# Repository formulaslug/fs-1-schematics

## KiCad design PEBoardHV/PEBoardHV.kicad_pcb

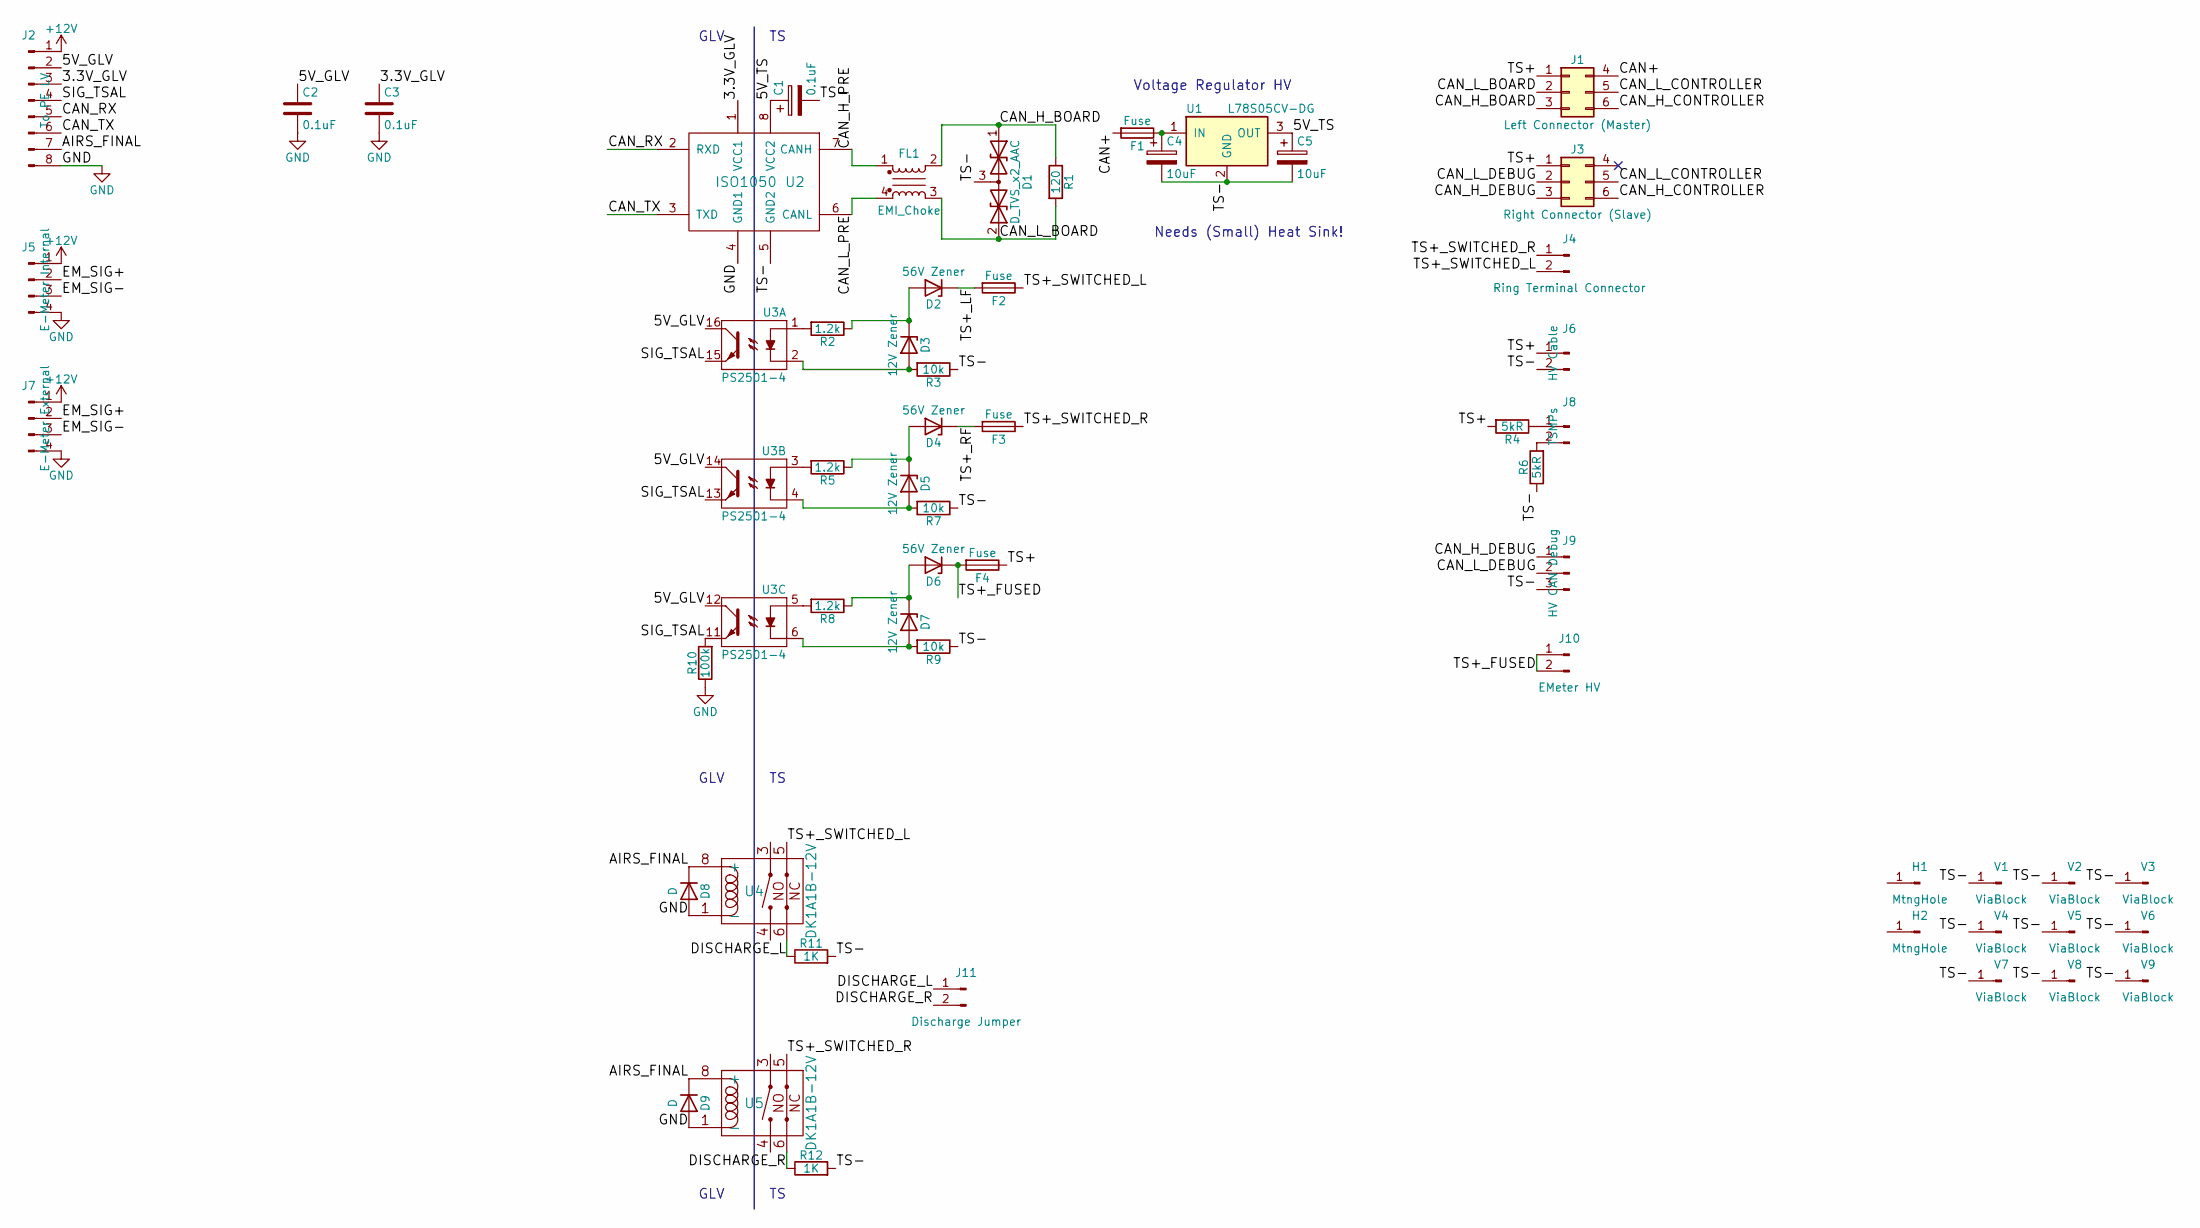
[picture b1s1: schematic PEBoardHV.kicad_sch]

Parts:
C1, C3: 0.1uF; C_Disc_D4.3mm_W1.9mm_P5.00mm
C2: 0.1uF; C_Disc_D3.0mm_W1.6mm_P2.50mm
C4, C5: 10uF; CP_Radial_D5.0mm_P2.50mm
D1: D_TVS_x2_AAC; SOT-23_Handsoldering
D2, D4, D6: 56V Zener; D_A-405_P7.62mm_Horizontal
D3, D5, D7: 12V Zener; D_A-405_P7.62mm_Horizontal
D8, D9: D; D_1206
F1, F2, F3, F4: Fuse; SMD Fuse
FL1: EMI_Choke; L_CommonMode_Choke
H1, H2: MtngHole; MountingHole_4.5mm
J1: Left Connector (Master); Molex_NanoFit_2x03x2.50mm_Straight
J2: To PE LV; Molex_NanoFit_2x04x2.50mm_Straight
J3: Right Connector (Slave); Molex_NanoFit_2x03x2.50mm_Straight
J4: Ring Terminal Connector; Molex_NanoFit_1x02x2.50mm_Straight
J5: E-Meter Internal; Molex_NanoFit_2x02x2.50mm_Straight
J6: HV Cable; Molex_NanoFit_1x02x2.50mm_Straight
J7: E-Meter External; DT15-4P
J8: TSMPs; DT15-2P
J9: HV CAN Debug; Molex_NanoFit_1x03x2.50mm_Straight
J10: EMeter HV; Molex_NanoFit_1x02x2.50mm_Straight
J11: Discharge Jumper; Pin_Header_Straight_2x01_Pitch2.54mm
R1: 120; R_0805_HandSoldering
R2, R5, R8: 1.2k; R_Axial_DIN0207_L6.3mm_D2.5mm_P10.16mm_Horizontal
R3, R7, R9: 10k; R_Axial_DIN0411_L9.9mm_D3.6mm_P12.70mm_Horizontal
R4, R6: 5kR; R_Axial_DIN0414_L11.9mm_D4.5mm_P20.32mm_Horizontal
R10: 100k; R_Axial_DIN0207_L6.3mm_D2.5mm_P10.16mm_Horizontal
R11, R12: 1K; TO-220-2_Horizontal_HeatSunk
U1: L78S05CV-DG; TO-220-3_Horizontal_HeatSunk
U2: ISO1050; DIP-8_W8.89mm_SMDSocket_LongPads
U3: PS2501-4; DIP-16_W7.62mm
U4, U5: DK1A1B-12V
V1, V2, V3, V4, V5, V6, V7, V8, V9: ViaBlock; ViaBlock-0.8mm

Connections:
+12V: J2.1, J5.1, J7.1
/3.3V_GLV: C3.1, J2.3, U2.1 (VCC1)
/5V_GLV: C2.1, J2.2, U3.12, U3.14, U3.16
/5V_TS: C1.1, C5.1, U1.3 (OUT), U2.8 (VCC2)
/AIRS_FINAL: D8.1 (K), D9.1 (K), J2.7, U4.8 (+), U5.8 (+)
/CAN+: F1.2, J1.4
/CAN_H_BOARD: D1.1 (A1), FL1.2, J1.3, R1.1
/CAN_H_CONTROLLER: J1.6, J3.6
/CAN_H_DEBUG: J3.3, J9.1
/CAN_H_PRE: FL1.1, U2.7 (CANH)
/CAN_L_BOARD: D1.2 (A2), FL1.3, J1.2, R1.2
/CAN_L_CONTROLLER: J1.5, J3.5
/CAN_L_DEBUG: J3.2, J9.2
/CAN_L_PRE: FL1.4, U2.6 (CANL)
/CAN_RX: J2.5, U2.2 (RXD)
/CAN_TX: J2.6, U2.3 (TXD)
/DISCHARGE_L: J11.1, R11.1, U4.6
/DISCHARGE_R: J11.2, R12.1, U5.6
/EM_SIG+: J5.2, J7.2
/EM_SIG-: J5.3, J7.3
/SIG_TSAL: J2.4, R10.2, U3.11, U3.13, U3.15
/TS+: F4.1, J1.1, J3.1, J6.1, R4.2
/TS+_FUSED: D6.1 (K), F4.2, J10.1, J10.2
/TS+_LF: D2.1 (K), F2.2
/TS+_RF: D4.1 (K), F3.2
/TS+_SWITCHED_L: F2.1, J4.2, U4.5
/TS+_SWITCHED_R: F3.1, J4.1, U5.5
/TS-: C1.2, C4.2, C5.2, D1.3 (common), J6.2, J9.3, R3.1, R6.1, R7.1, R9.1, R11.2, R12.2, U1.2 (GND), U2.5 (GND2), V1.1, V2.1, V3.1, V4.1, V5.1, V6.1, V7.1, V8.1, V9.1
GND: C2.2, C3.2, D8.2 (A), D9.2 (A), J2.8, J5.4, J7.4, R10.1, U2.4 (GND1), U4.1 (-), U5.1 (-)
unnamed: C4.1, F1.1, U1.1 (IN)
unnamed: D2.2 (A), D3.1 (K), R2.1
unnamed: D3.2 (A), R3.2, U3.2
unnamed: D4.2 (A), D5.1 (K), R5.1
unnamed: D5.2 (A), R7.2, U3.4
unnamed: D6.2 (A), D7.1 (K), R8.1
unnamed: D7.2 (A), R9.2, U3.6
unnamed: J8.1, R4.1
unnamed: J8.2, R6.2
unnamed: R2.2, U3.1
unnamed: R5.2, U3.3
unnamed: R8.2, U3.5

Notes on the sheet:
Voltage Regulator HV
GLV TS
Needs (Small) Heat Sink!

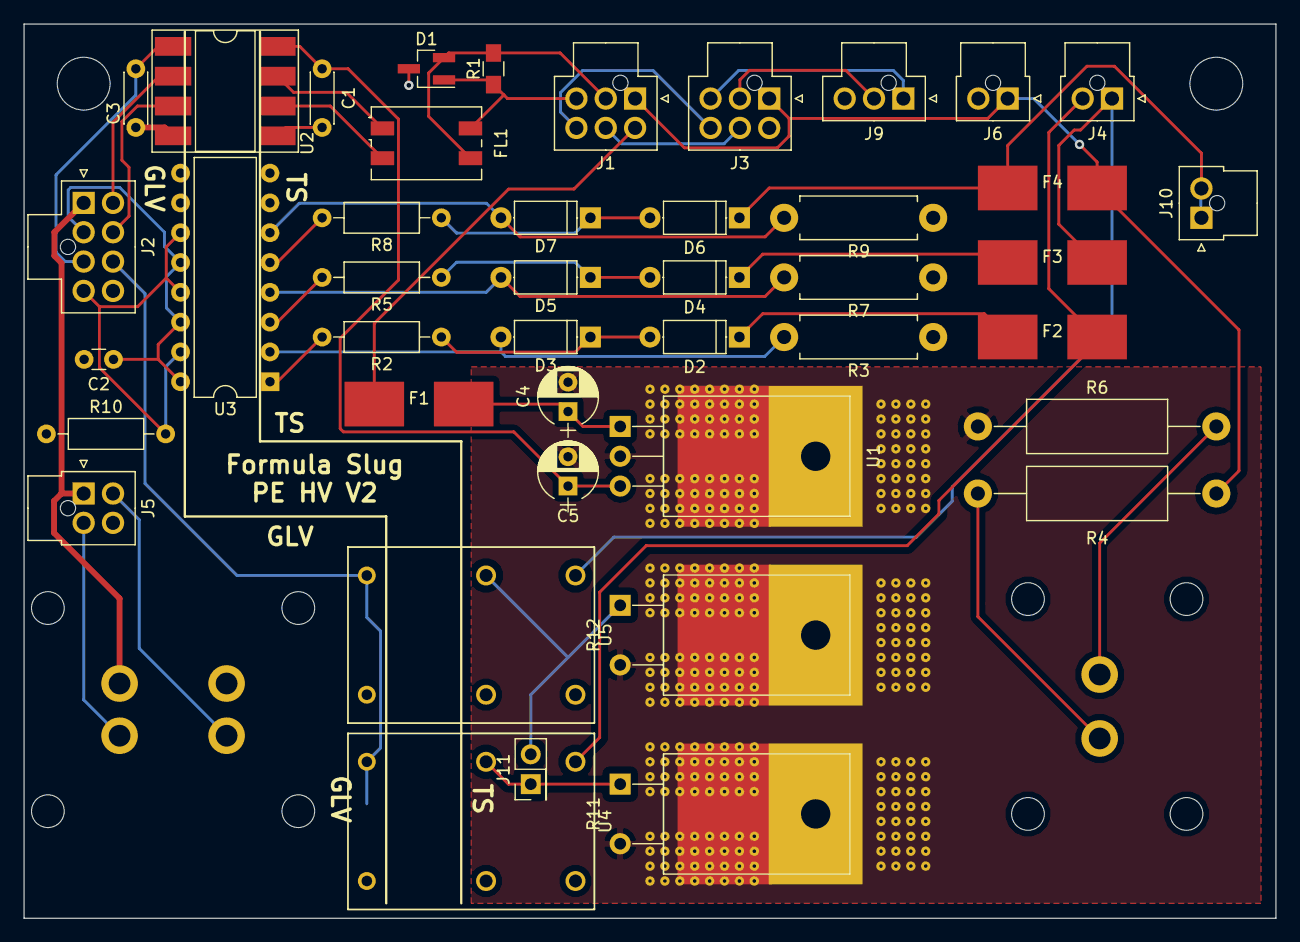
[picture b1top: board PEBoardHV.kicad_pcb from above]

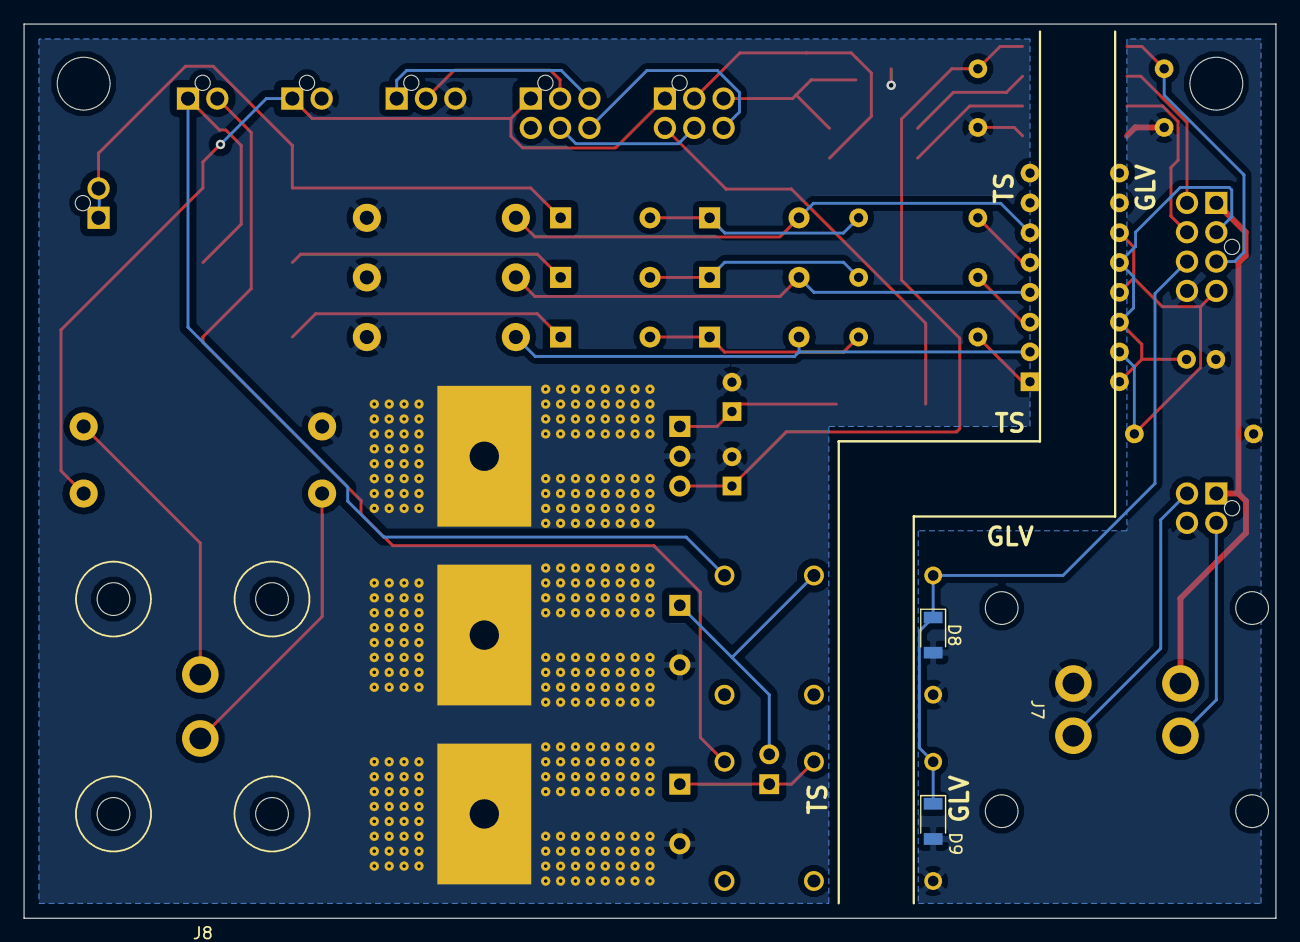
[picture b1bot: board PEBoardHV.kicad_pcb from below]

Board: 2 copper layers, 106.7 x 76.2 mm, 58 parts (4 on the bottom side), 41 nets.

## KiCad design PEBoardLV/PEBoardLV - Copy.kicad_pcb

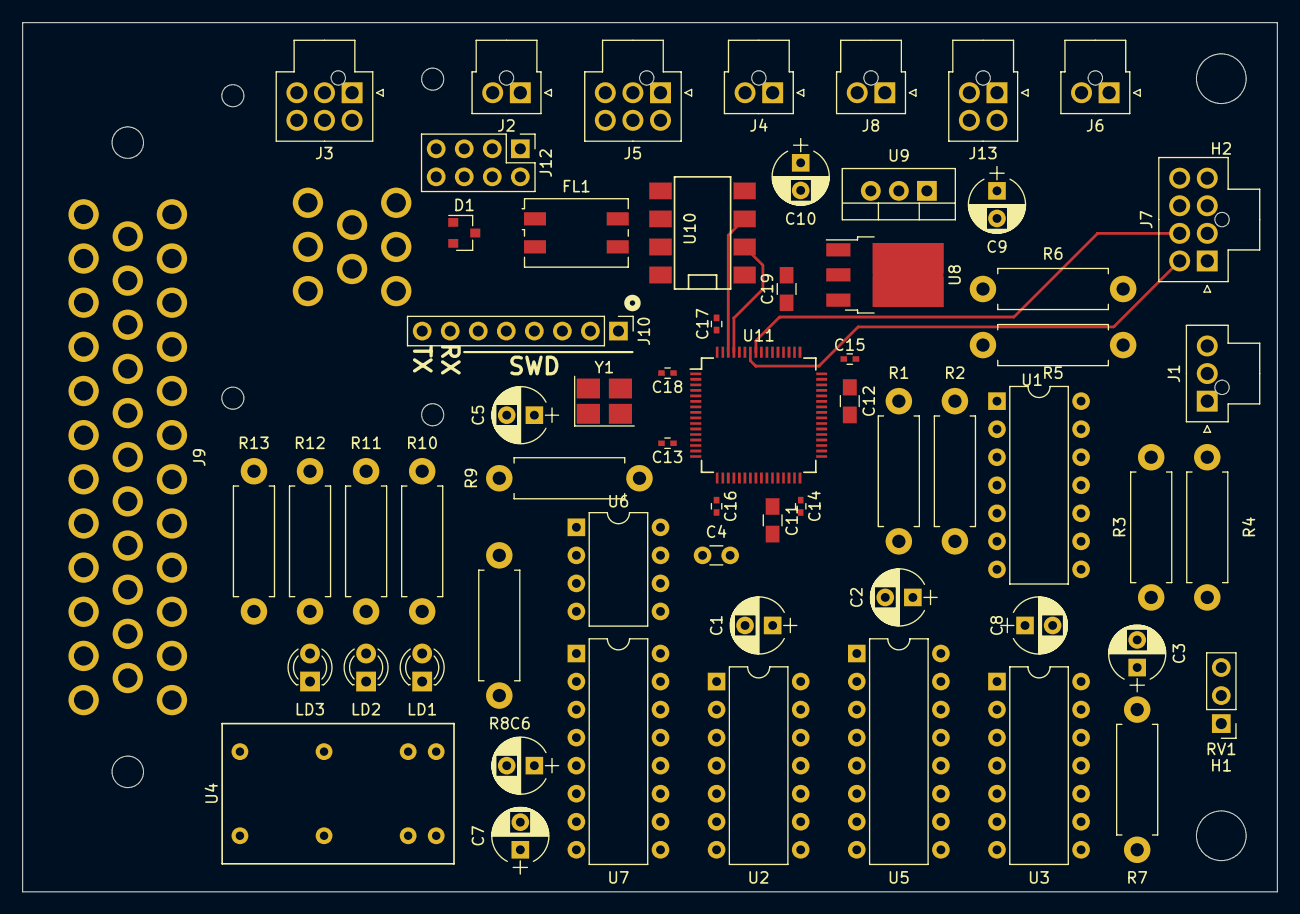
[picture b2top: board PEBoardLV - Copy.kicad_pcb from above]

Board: 2 copper layers, 113.7 x 78.7 mm, 65 parts (1 on the bottom side), 92 nets.

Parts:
C1, C2, C6, C7, C8: CP; CP_Radial_D5.0mm_P2.50mm
C3, C5, C9, C10: 10uF; CP_Radial_D5.0mm_P2.50mm
C4: 0.1uF; C_Disc_D3.0mm_W1.6mm_P2.50mm
C11, C12: 2.2uF; C_0805_HandSoldering
C13, C14, C15, C16, C17, C18: 0.1uF; C_0402
C19: 4.7uF; C_0805_HandSoldering
D1: D_TVS_x2_AAC; SOT-23
FL1: EMI_Filter_CommonMode; L_CommonMode_Wuerth_WE-SL2
H1, H2: MtngHole; MountingHole_4.5mm
J1: BSPD Test Jumper; Molex_NanoFit_1x03x2.50mm_Straight
J2: Beam Interlock; Molex_NanoFit_1x02x2.50mm_Straight
J3: To HV Interlocks; Molex_NanoFit_2x03x2.50mm_Straight
J4: To Left Panel; Molex_NanoFit_1x02x2.50mm_Straight
J5: To Right Panel; Molex_NanoFit_2x03x2.50mm_Straight
J6: To Brake Light; Molex_NanoFit_1x02x2.50mm_Straight
J7: To PE HV; Molex_NanoFit_2x04x2.50mm_Straight
J8: BSPD Reset; Molex_NanoFit_1x02x2.50mm_Straight
J9: Main LV Connector; Ampseal - 35 pin
J10: SWD Header; Pin_Header_Straight_1x08_Pitch2.54mm
J11: ECU Debug Connector; Ampseal-776276-1
J12: Extra Pin Header; Pin_Header_Straight_2x04_Pitch2.54mm
J13: To TSAL; Molex_NanoFit_2x02x2.50mm_Straight
LD1, LD2, LD3: LED; LED_D3.0mm
R1, R2, R3, R4, R5, R6: R; R_Axial_DIN0411_L9.9mm_D3.6mm_P12.70mm_Horizontal
R7: 100k; R_Axial_DIN0411_L9.9mm_D3.6mm_P12.70mm_Horizontal
R8: 4.7kR; R_Axial_DIN0411_L9.9mm_D3.6mm_P12.70mm_Horizontal
R9: 18k; R_Axial_DIN0411_L9.9mm_D3.6mm_P12.70mm_Horizontal
R10, R11, R12: 330; R_Axial_DIN0411_L9.9mm_D3.6mm_P12.70mm_Horizontal
R13: 2.2k; R_Axial_DIN0411_L9.9mm_D3.6mm_P12.70mm_Horizontal
RV1: POT; Pin_Header_Straight_1x03_Pitch2.54mm
U1: MCP6004; DIP-14_W7.62mm
U2: 4072; DIP-14_W7.62mm
U3: 4071; DIP-14_W7.62mm
U4: DE1A1B-L2-12V
U5: 74HC595; DIP-16_W7.62mm
U6: LM555N; DIP-8_W7.62mm
U7: SN754410; DIP-16_W7.62mm
U8: NCP1117DT33RKG; TO-252-3_TabPin2
U9: L78S05CV-DG; TO-220-3_Vertical
U10: ISO1050; DIP-8_SMD
U11: STM32F405; LQFP-64_10x10mm_Pitch0.5mm
Y1: 8MHz; Crystal_SMD_3225-4pin_3.2x2.5mm_HandSoldering

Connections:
+3V3: C13.1, C14.1, C15.1, C16.1, C17.1, C18.1, C19.1, J7.3, J9.14, J9.20, J10.1, J11.1, R5.1, R13.1, RV1.1, U1.9, U8.3, U10.1, U11.1, U11.13, U11.19, U11.32, U11.48, U11.64, Y1.4
+5V: C1.1, C2.1, C6.1, C8.1, C10.1, J7.2, R7.1, R8.1, U1.4, U2.14, U3.14, U5.10, U5.16, U6.4, U6.8, U7.1, U7.9, U7.16, U9.3, U10.8
+12V: C7.1, C9.1, J7.1, J9.1, J9.2, J9.23, J13.1, U7.8, U8.1, U9.1
/5V_BMS: J9.9, R2.2, R3.1
/12V_LVMS: J5.2, J9.24
/12V_SRC: J5.1, J9.3
/AIRS_3PHASE_OUT: J3.4, J3.5
/AIRS_ACC_OUT: J4.1, J9.7
/AIRS_BEAM_OUT: J2.2, J3.1
/AIRS_BOTS_OUT: J9.13, U4.5
/AIRS_BSPD_OUT: J2.1, U4.6
/AIRS_DASH_OUT: J9.12, J9.30
/AIRS_FINAL: J5.4, J7.7, J9.8
/AIRS_LEFTESTOP_OUT: J4.2, J5.3
/AIRS_PEINTERLOCKS_OUT: J3.6, J9.6
/BRAKELT_H: J6.1, U7.11, U7.14
/BSPD_BRAKE: U1.7, U3.2
/BSPD_CURRENT: U1.1, U3.1
/BSPD_FLT: U3.4, U7.2
/BSPD_FLT_H: U4.8, U7.3
/BSPD_FLT_LATCHED: U4.3, U11.35
/BSPD_RESET: J8.1, U4.7
/BSPD_SIG: U3.3, U5.14
/BUTTON_1: J9.27, U11.30
/BUTTON_2: J9.28, U11.33
/BUTTON_3: J9.29, U11.34
/CAN_H: D1.2, FL1.2, J9.4, J9.25
/CAN_L: D1.1, FL1.4, J9.5, J9.26
/CAN_RX_GLV: U10.2, U11.61
/CAN_RX_TS: J7.6, U11.57
/CAN_TX_GLV: U10.3, U11.62
/CAN_TX_TS: J7.5, U11.58
/CLK: U5.11, U5.12, U6.3
/LED_AMS: J9.31, U11.41
/LED_BSPD: J9.33, U11.37
/LED_IMD: J9.32, U11.50
/NRST: J10.5, J11.5, U11.7
/PA4: J12.5, U11.20
/PA5: J12.6, U11.21
/PA7: J12.7, U11.23
/PC0: J12.1, U11.8
/PC1: J12.2, U11.9
/PC2: J12.3, U11.10
/PC3: J12.4, U11.11
/PC4: J12.8, U11.24
/SIG_APPS_A: J9.15, U11.16
/SIG_APPS_B: J9.18, U11.17
/SIG_BRAKELT: U7.10, U7.15, U11.40
/SIG_BSE: J9.21, U1.6, U11.15
/SIG_CURRENT: J1.3, J9.10
/SIG_RTDS: J13.3, U11.39
/SIG_STEER: J9.34, U11.22
/SIG_TSAL: J7.4, J13.2
/STATUS_LED_1: R10.2, U11.28
/STATUS_LED_2: R11.2, U11.27
/STATUS_LED_3: R12.2, U11.26
/SWCLK: J10.2, J11.2, U11.49
/SWDIO: J10.4, J11.4, U11.46
/SWO: J10.6, J11.6, U11.55
/TIMER: U1.8, U7.7
/TIMER_H: U4.1, U4.2, U7.6
/UART_RX: J10.7, J11.7, U11.52
/UART_TX: J10.8, J11.8, U11.51
/VCAP_1: C11.1, U11.31
/VCAP_2: C12.1, U11.47
/XTAL: U11.5, Y1.3
GND: C1.2, C2.2, C3.2, C4.2, C5.2, C6.2, C7.2, C8.2, C9.2, C10.2, C11.2, C12.2, C13.2, C14.2, C15.2, C16.2, C17.2, C18.2, C19.2, D1.3, J5.5, J6.2, J7.8, J8.2, J9.11, J9.16, J9.19, J9.22, J9.35, J10.3, J11.3, J13.4, LD1.1, LD2.1, LD3.1, R1.1, R4.2, R6.2, RV1.3, U1.11, U2.7, U3.7, U4.4, U5.8, U5.13, U6.1, U7.4, U7.5, U7.12, U7.13, U8.2, U9.2, U10.4, U10.5, U11.12, U11.18, U11.29, U11.60, U11.63, Y1.2
unnamed: C3.1, R7.2, U1.10
unnamed: C4.1, U6.5
unnamed: C5.1, R9.2, U6.2, U6.6
unnamed: FL1.1, U10.7
unnamed: FL1.3, U10.6
unnamed: J1.1, R3.2, R4.1
unnamed: J1.2, U1.2
unnamed: J3.2, J3.3
unnamed: J9.17, R13.2
unnamed: LD1.2, R10.1
unnamed: LD2.2, R11.1
unnamed: LD3.2, R12.1
unnamed: R1.2, R2.1, U1.3
unnamed: R5.2, R6.1, RV1.2, U1.5
unnamed: R8.2, R9.1, U6.7
unnamed: U2.1, U3.5
unnamed: U2.2, U5.15
unnamed: U2.3, U5.1
unnamed: U2.4, U5.2
unnamed: U2.5, U5.3
unnamed: U2.9, U5.4
unnamed: U2.10, U5.5
unnamed: U2.11, U5.6
unnamed: U2.12, U5.7
unnamed: U2.13, U3.6

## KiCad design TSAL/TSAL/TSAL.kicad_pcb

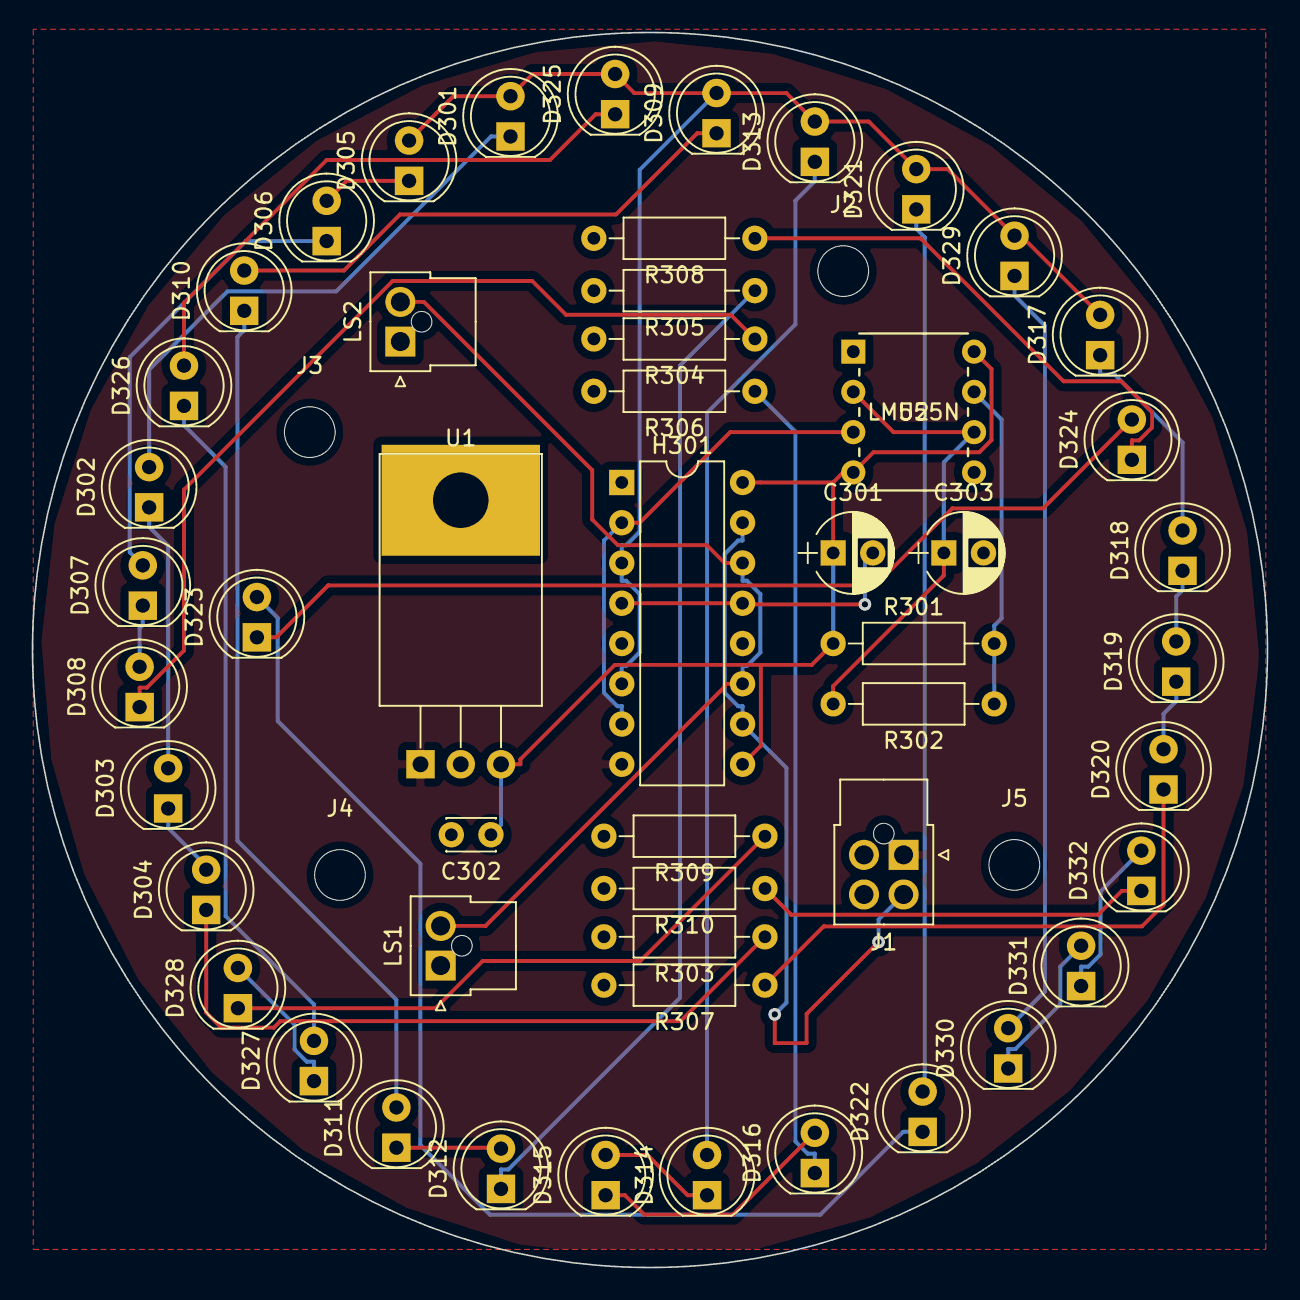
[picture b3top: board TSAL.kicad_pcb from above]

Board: 2 copper layers, 77.9 x 77.9 mm, 55 parts (0 on the bottom side), 41 nets.

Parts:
C301, C303: 10uF; CP_Radial_D5.0mm_P2.50mm
C302: .47uF; C_Disc_D3.0mm_W2.0mm_P2.50mm
D301, D302, D303, D304, D305, D306, D307, D308, D309, D310, D311, D312, D313, D314, D315, D316, D317, D318, D319, D320, D321, D322, D323, D324, D325, D326, D327, D328, D329, D330, D331, D332: Led_Small; LED_D5.0mm
H301: SN754410; DIP-16_W7.62mm
J1: CONN_01X04; Molex_NanoFit_2x02x2.50mm_Straight
J2, J3, J4, J5: Conn_01x01; MountingHole_3.2mm_M3
LS1, LS2: RTDS Piezo; Molex_NanoFit_1x02x2.50mm_Straight
R301, R302: 15K; R_Axial_DIN0207_L6.3mm_D2.5mm_P10.16mm_Horizontal
R303, R304, R305, R306, R307, R308, R309, R310: 180; R_Axial_DIN0207_L6.3mm_D2.5mm_P10.16mm_Horizontal
U1: L78S05CV-DG; TO-220-3_Horizontal_HeatSunk
U2: LM555N; LM555CN

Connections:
+5V: C301.1, C302.1, H301.9, H301.16, R301.1, U1.3, U2.4, U2.8
+12V: H301.8, J1.1, U1.1
/OSC: D301.2, D305.2, D309.2, D313.2, D317.2, D321.2, D325.2, D329.2, H301.3, H301.6
/RTDS_H: H301.11, H301.14, LS1.2, LS2.2
/SIG_RTDS: H301.10, H301.15, J1.3
GND: C301.2, C302.2, C303.2, H301.4, H301.5, H301.12, H301.13, J1.4, LS1.1, LS2.1, R303.2, R304.2, R305.2, R306.2, R307.2, R308.2, R309.2, R310.2, U1.2, U2.1
unnamed: C303.1, R302.2, U2.2, U2.6
unnamed: D301.1, D302.2
unnamed: D302.1, D303.2
unnamed: D303.1, D304.2
unnamed: D304.1, R303.1
unnamed: D305.1, D306.2
unnamed: D306.1, D307.2
unnamed: D307.1, D308.2
unnamed: D308.1, R304.1
unnamed: D309.1, D310.2
unnamed: D310.1, D311.2
unnamed: D311.1, D312.2
unnamed: D312.1, R305.1
unnamed: D313.1, D314.2
unnamed: D314.1, D315.2
unnamed: D315.1, D316.2
unnamed: D316.1, R306.1
unnamed: D317.1, D318.2
unnamed: D318.1, D319.2
unnamed: D319.1, D320.2
unnamed: D320.1, R307.1
unnamed: D321.1, D322.2
unnamed: D322.1, D323.2
unnamed: D323.1, D324.2
unnamed: D324.1, R308.1
unnamed: D325.1, D326.2
unnamed: D326.1, D327.2
unnamed: D327.1, D328.2
unnamed: D328.1, R309.1
unnamed: D329.1, D330.2
unnamed: D330.1, D331.2
unnamed: D331.1, D332.2
unnamed: D332.1, R310.1
unnamed: H301.2, H301.7, U2.3
unnamed: R301.2, R302.1, U2.7

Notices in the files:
parts and their libraries:
Copyright 2016 Accelerated Designs. All rights reserved.
